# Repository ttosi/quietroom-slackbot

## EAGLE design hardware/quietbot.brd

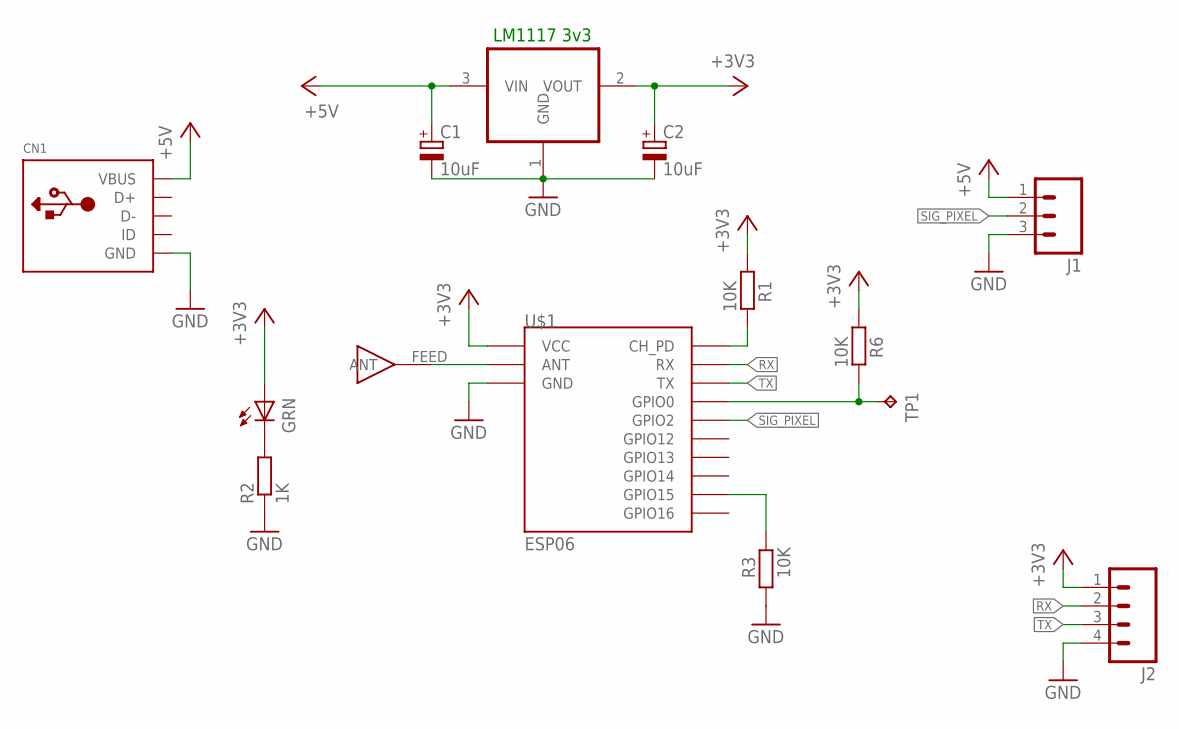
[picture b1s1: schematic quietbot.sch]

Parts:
C1, C2: 10uF; R/2012-12R
CN1: USBMINIB; USB-MINIB
IC2: REG1117; SOT223; MPN LM1117 3v3
J1: M031X03_NO_SILK; 1X03_NO_SILK
J2: M04NO_SILK_ALL_ROUND; 1X04_NO_SILK_ALL_ROUND
LED2: GRN; CHIP-LED0805
R1, R3, R6: 10K; R0805
R2: 1K; R0805
TP1: TPTP15R; TP15R
U$1: ESP06
U$2: ANT; ANTENNA-CERAMIC

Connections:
+3V3: C2.+, IC2.2 (VOUT), J2.1, LED2.A, R1.1, R6.1, U$1.VCC
+5V: C1.+, CN1.VBUS, IC2.3 (VIN), J1.1
GND: C1.-, C2.-, CN1.GND, IC2.1 (GND), J1.3, J2.4, R2.1, R3.1, U$1.GND6 (GND7)
unnamed: R3.2, U$1.GPIO15
unnamed: LED2.C, R2.2
unnamed: U$1.ANT, U$2.FEED
unnamed: R6.2, TP1.TP, U$1.GPIO0
unnamed: R1.2, U$1.CH_PD
RX: J2.2, U$1.RX
SIG_PIXEL: J1.2, U$1.GPIO2
TX: J2.3, U$1.TX

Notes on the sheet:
LM1117 3v3

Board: 2 copper layers, 14 parts (0 on the bottom side), 11 nets, no tracks yet.

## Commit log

2016-09-02 commands with actions()
2016-09-03 workon desks, start users
2016-09-03 desks work. stuck on assignment handling
2016-09-03 updating help text
2016-09-03 leave, assign & list commands
2016-09-04 add occupied time to desk list
2016-09-04 refactor bot.js & commands.js, add TODO.md
2016-09-04 add esp8226 firmware
2016-09-05 esp firmware
2016-09-05 client started, not tested
2016-09-06 client.js
2016-09-06 server
2016-09-06 remove sugarjs for objects add lodash
2016-09-06 replace sugar object with lodash
2016-09-07 firmware add config.txt, remove replace sugar.object w/ lodash
2016-09-07 todo
2016-09-08 add connection checking, refactoring
2016-09-08 accept @[username] (not working)
2016-09-09 2 clients connectedgit add .
2016-09-09 rework command in bot.js
2016-09-10 add hardware
2016-09-10 add eagle files
2016-09-10 hardware
2016-09-11 cleanup
2016-10-22 parse userid in User.get()
2016-10-23 completed bot send command to desk
2016-10-25 commands show on pixels
2016-10-25 send commands to desk
2016-10-25 update file
2016-10-25 update todo
2016-11-01 add qb schematic & board
2016-11-01 rename board & schematic
2016-11-01 board design
2016-12-05 minor updates
2016-12-05 minor changes

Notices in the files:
parts and their libraries:
SparkFun-Connectors: Licensing: Creative Commons ShareAlike 4.0 International - https://creativecommons.org/licenses/by-sa/4.0
